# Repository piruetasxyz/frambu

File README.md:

# frambu

placa de desarrollo abierta basada en el microcontrolador **RP2040** de Raspberry Pi,
diseñada en [KiCad](https://www.kicad.org/) para fabricarse y ensamblarse en
[JLCPCB](https://jlcpcb.com/).

la documentación, con capturas del esquemático, de la placa y la lista de
materiales, está publicada en
[piruetasxyz.github.io/frambu](https://piruetasxyz.github.io/frambu/) y en
[`docs/frambu.md`](docs/frambu.md).

este repositorio se usa para trabajo colaborativo y también como material de
enseñanza: la idea es que cualquier persona pueda clonarlo, abrirlo, entender cómo
está hecho y modificarlo.

## contenidos

- [estado del proyecto](#estado-del-proyecto)
- [características de la placa](#características-de-la-placa)
- [estructura del repositorio](#estructura-del-repositorio)
- [automatizaciones (GitHub Actions)](#automatizaciones-github-actions)
- [requisitos](#requisitos)
- [cómo abrir el proyecto](#cómo-abrir-el-proyecto)
- [biblioteca local de KiCad](#biblioteca-local-de-kicad)
- [cómo trabajar en conjunto](#cómo-trabajar-en-conjunto)
- [pendientes conocidos](#pendientes-conocidos)
- [comentarios de revisión (2026-11-10)](#comentarios-de-revisión-2026-11-10)
- [glosario](#glosario)
- [recursos para aprender](#recursos-para-aprender)
- [licencia](#licencia)

## estado del proyecto

**revisión A, en diseño.** el esquemático está avanzado y la placa se está
rehaciendo desde cero: por ahora no tiene contorno, componentes ni pistas. no
está lista para fabricar.

| revisión | carpeta | estado |
| --- | --- | --- |
| A | [`frambu-v-0-rev-a/`](frambu-v-0-rev-a/) | en diseño |

## características de la placa

| bloque | componente | notas |
| --- | --- | --- |
| microcontrolador | RP2040 (U2), LQFN-56 7×7 mm | doble núcleo ARM Cortex-M0+, hasta 133 MHz |
| memoria flash | W25Q128JVS (U1), SOIC-8 | 128 Mbit (16 MB), conectada por QSPI |
| reloj | cristal Y1 de 12 MHz (ABM8-272-T3) + condensadores de 15 pF (C1, C2) | señales `XIN` / `XOUT` |
| USB | conector USB-C 16 pines (J1) | USB 2.0; resistencias de 5,1 kΩ en CC1/CC2 (R3, R4) para que el cable entregue 5 V; resistencias en serie de 27 Ω en `USB_D+`/`USB_D-` (R6, R7) |
| alimentación | regulador lineal AMS1117 (U3) | de `VBUS` (5 V del USB) a `+3V3`; el RP2040 genera internamente `+1V1` para su núcleo |
| botón | SW1 (PTS636) | botón de arranque (BOOTSEL), en la línea `QSPI_SS` |
| pines | J2 y J5, conectores hembra 1×20 de 2,54 mm | mismo pinout que la Raspberry Pi Pico: J2 son los pines 1–20 y J5 los pines 40–21 (el pin 1 de J5 es `VBUS`, así ambos conectores tienen el pin 1 en el mismo extremo). `VSYS` y `3V3_EN` quedan sin conexión |
| depuración | J3, conector macho 1×3 de 2,54 mm | `SWCLK`, `GND`, `SWD`, en el mismo orden que la Pico |
| GPIO extra | J4, conector hembra 1×4 de 2,54 mm | `GPIO23`, `GPIO24`, `GPIO25` y `GPIO29_ADC3`, que la Pico no expone |
| fijación | H1, H2 | agujeros para tornillos M3 |
| placa | 2 capas de cobre (`F.Cu`, `B.Cu`) | tamaño por definir: se está rehaciendo desde cero |

el diseño sigue de cerca la guía oficial
[Hardware design with RP2040](https://datasheets.raspberrypi.com/rp2040/hardware-design-with-rp2040.pdf),
que es la mejor referencia para entender por qué cada componente está ahí.

## estructura del repositorio

```text
frambu/
├── README.md                     este archivo
├── LICENSE                       licencia MIT
├── .gitignore                    ignora archivos temporales y de respaldo de KiCad
├── .github/workflows/            automatizaciones de GitHub Actions
├── docs/
│   ├── frambu.md              capturas y lista de materiales (BOM) de la placa
│   ├── generar_bom.py            regenera la tabla de BOM en frambu.md
│   └── images/                   capturas SVG generadas automáticamente
└── frambu-v-0-rev-a/              una carpeta por revisión de la placa
    ├── frambu-v-0-rev-a.kicad_pro proyecto de KiCad (abrir este)
    ├── frambu-v-0-rev-a.kicad_sch esquemático
    ├── frambu-v-0-rev-a.kicad_pcb diseño de la placa (PCB)
    ├── bom.csv                   lista de partes de JLCPCB, escrita a mano
    ├── sym-lib-table             registra la biblioteca local de símbolos
    ├── fp-lib-table              registra la biblioteca local de huellas
    └── bibliotecas/              biblioteca local generada desde bom.csv
        ├── frambu-v-0-rev-a.kicad_sym   símbolos
        ├── frambu-v-0-rev-a.pretty/     huellas (footprints)
        └── frambu-v-0-rev-a.3dshapes/   modelos 3D (.step y .wrl)
```

cada revisión vive en su propia carpeta para poder comparar versiones y no perder
el diseño de una placa ya fabricada.

## automatizaciones (GitHub Actions)

hay dos workflows en [`.github/workflows/`](.github/workflows/):

- [`actualizar-capturas.yml`](.github/workflows/actualizar-capturas.yml): cada
  vez que se hace push a `main` con cambios en el esquemático o la placa de la
  revisión activa, usa `kicad-cli` (KiCad 10, en docker) para exportar
  `docs/images/frambu-v-0-rev-a-esquematico.svg` y
  `docs/images/frambu-v-0-rev-a-placa.svg`, regenera la tabla de BOM en
  `docs/frambu.md` con `docs/generar_bom.py`, y hace commit de los cambios.
- [`desplegar-paginas.yml`](.github/workflows/desplegar-paginas.yml): construye
  el sitio con Jekyll y lo publica en GitHub Pages, tanto en cada push a `main`
  como al terminar el workflow anterior.

como el primer workflow hace commits, **conviene hacer `git pull` después de
cada push** que toque el esquemático o la placa.

la tabla de BOM también se puede regenerar a mano, con KiCad 10 instalado:

```bash
python3 docs/generar_bom.py
```

si se agrega una revisión nueva (por ejemplo `frambu-v-0-rev-b/`), hay que
actualizar las rutas en `actualizar-capturas.yml` y `REVISION` en
`docs/generar_bom.py`.

## requisitos

- **KiCad 10** o superior. los archivos se guardaron con KiCad 10.0 y no se
  pueden abrir en versiones anteriores.
- **git**, para clonar y colaborar.
- opcional, solo para regenerar la biblioteca local: **Python 3** y el
  repositorio [partes-jlcpcb](https://github.com/piruetasxyz/partes-jlcpcb).

## cómo abrir el proyecto

```bash
git clone https://github.com/piruetasxyz/frambu.git
cd frambu
```

luego, en KiCad: **Archivo → Abrir proyecto** y elegir
`frambu-v-0-rev-a/frambu-v-0-rev-a.kicad_pro`. desde ahí se abren el esquemático y
la placa.

no hace falta configurar nada más: los archivos `sym-lib-table` y `fp-lib-table`
del proyecto ya apuntan a la biblioteca local usando `${KIPRJMOD}`, que KiCad
reemplaza por la carpeta del proyecto. por eso funciona en cualquier computador,
sin importar dónde se clone el repositorio.

## biblioteca local de KiCad

las partes que usamos de JLCPCB se listan en `bom.csv` dentro de cada revisión
(por ejemplo `frambu-v-0-rev-a/bom.csv`). tiene las mismas columnas que el
inventario de [partes-jlcpcb](https://github.com/piruetasxyz/partes-jlcpcb):

| columna | significado |
| --- | --- |
| `Category` | tipo de componente |
| `Value` | valor (ej. `10kΩ`, `100nF`) o número de parte |
| `Footprint` | encapsulado (ej. `0402`, `SOIC-8`) |
| `JLCPCB Part #` | código LCSC, empieza con `C` (ej. `C25744`) |
| `Description` | descripción de JLCPCB |
| `Qty (fecha)` | cantidad en nuestro inventario en esa fecha; vacía si no la tenemos |

a partir de ese archivo se genera la biblioteca local (símbolos, huellas y
modelos 3D):

```bash
cd frambu-v-0-rev-a
python3 /ruta/a/partes-jlcpcb/generar_biblioteca.py --bom bom.csv --output bibliotecas/frambu-v-0-rev-a
```

ajusta `/ruta/a/partes-jlcpcb` a donde tengas clonado ese repositorio. requiere
su entorno virtual activado (ver su README).

### agregar una parte nueva

1. buscar la parte en [jlcpcb.com/parts](https://jlcpcb.com/parts) y anotar su
   código LCSC (`C…`). preferir partes **básicas** (*basic*) antes que
   **extendidas** (*extended*): las extendidas cobran un recargo de montaje por
   cada tipo de parte.
2. agregar una fila a `bom.csv`.
3. regenerar la biblioteca con el comando de arriba.
4. en el esquemático, usar el símbolo de la biblioteca `frambu-v-0-rev-a` o
   asignar la huella nueva al símbolo existente, y llenar su campo `LCSC` con el
   código de la parte.
5. hacer commit de `bom.csv` **y** de los archivos nuevos en `bibliotecas/`
   juntos, para que la otra persona no abra el proyecto con huellas faltantes.

## cómo trabajar en conjunto

los archivos de KiCad son texto, así que git los guarda bien, pero **no se
pueden fusionar (merge) de forma confiable**: si dos personas editan el mismo
`.kicad_sch` o `.kicad_pcb` a la vez, el conflicto casi siempre hay que
resolverlo a mano rehaciendo uno de los cambios. para evitarlo:

1. **avisar antes de editar.** decir quién está trabajando en el esquemático o
   en la placa, y no editar el mismo archivo al mismo tiempo.
2. **traer cambios antes de abrir KiCad:** `git pull`.
3. **cerrar KiCad antes de hacer commit**, para que todo esté guardado.
4. **commits pequeños y con mensajes claros**, en español y en minúsculas,
   describiendo el cambio (ej. `agregar cristal, mounting holes`).
5. **subir los cambios pronto:** `git push`, para que la otra persona los tenga.
6. para cambios grandes o experimentales, usar una rama y un pull request.

el `.gitignore` ya ignora lo que KiCad genera localmente y no debe subirse:
respaldos (`*-backups`), archivos de bloqueo (`~*.lck`), cachés,
`*.kicad_prl` (preferencias de ventana de cada persona) y archivos exportados
(`*.csv`, `*.xml`, `*.net`). la excepción es `bom.csv`, que sí se sube porque
lo escribimos a mano.

si KiCad dice que un archivo está bloqueado por otro usuario, probablemente
quedó un `~*.lck` de una sesión que se cerró mal; se puede borrar con KiCad
cerrado.

### antes de dar por terminada una revisión

- [ ] el esquemático pasa el **ERC** (Inspeccionar → Verificador de reglas
      eléctricas) sin errores.
- [ ] la placa pasa el **DRC** (Inspeccionar → Verificador de reglas de diseño)
      sin errores, usando las reglas de fabricación de JLCPCB.
- [ ] todos los componentes a ensamblar tienen código LCSC y huella que
      coincide con esa parte.
- [ ] la placa coincide con el esquemático (Herramientas → Actualizar PCB desde
      el esquemático, sin cambios pendientes).
- [ ] revisado en el visor 3D.

## pendientes conocidos

revisión A, a la fecha de este documento:

- la placa está vacía: falta dibujar el contorno en `Edge.Cuts` (antes era de
  50 × 60 mm), traer las huellas desde el esquemático (`F8`), ubicarlas y rutear.
- varias partes del esquemático no están en el inventario de
  [`partes-jlcpcb`](https://github.com/piruetasxyz/partes-jlcpcb), solo en su
  lista de deseos: U3 (`C880752`), R2 (`C25744`), C3, C7, C18 (`C15525`),
  R6, R7 (`C25100`), C1, C2 (`C1548`), Y1 (`C20625731`) y los condensadores de
  100 nF C5, C8–C12, C15, C16, C19 (`C307331`).
- al ubicar J2 y J5, sus pines 1 van en el mismo extremo de la placa, separados
  por 17,78 mm (7 × 2,54 mm) como en la Pico, para que sea compatible con sus
  accesorios.
- `VSYS` (pin 39 de la Pico) queda sin conexión. para alimentar la placa por ahí,
  como en la Pico, falta un diodo Schottky de `VBUS` a `VSYS` y alimentar U3
  desde `VSYS`.

## comentarios de revisión (2026-11-10)

notas de la revisión de hoy, para que alguien más las revise antes de mandar a
fabricar.

### cambios hechos

- **anillos anulares:** tres vías de `GND` medían 0,45 mm con taladro de 0,3 mm
  (anillo de 0,075 mm, el mínimo es 0,1 mm). se agrandaron a 0,6 mm, como el
  resto de las vías. después se corrigieron a mano los problemas de margen que
  eso generó.
- **C16** (100 nF, desacople de `+3V3`) estaba en el esquemático pero no en la
  placa; ya está ubicado y ruteado.
- **GPIO23, GPIO24, GPIO25 y GPIO29_ADC3** del RP2040 ahora están marcados como
  sin conexión (`X`) en el esquemático, y sus pads en la placa coinciden. en la
  Pico esos pines se usan internamente y no salen a los conectores. se prefirió
  dejarlos sin conexión en vez de llevarlos a `GND`, porque si el firmware los
  configura como salida en alto quedarían en corto.
- **archivos de fabricación:** nuevo script
  [`docs/generar_fabricacion.py`](docs/generar_fabricacion.py), que genera con
  `kicad-cli` las mismas carpetas que se usaron en
  [tacto48](https://github.com/piruetasxyz/tacto48):
  - [`frambu-v-0-rev-a-fab/`](frambu-v-0-rev-a-fab/): gerbers, taladros (PTH y
    NPTH), `gbrjob` y `frambu-v-0-rev-a-gerb.zip`, que es lo que se sube a
    JLCPCB como "Gerber file".
  - [`frambu-v-0-rev-a-pcba/`](frambu-v-0-rev-a-pcba/): `bom.csv` y `cpl.csv`
    para "PCB Assembly". entran todas las partes con el campo `LCSC` lleno en el
    esquemático; J2, J3 y J5 (conectores de 2,54 mm) quedan fuera y se sueldan
    a mano.
  - se regeneran con `python3 docs/generar_fabricacion.py` (requiere KiCad 10).
  - el `.gitignore` ahora deja pasar `*-pcba/*.csv`.

estado al cerrar la revisión: el DRC no tiene errores ni conexiones pendientes,
la placa coincide con el esquemático, y el ERC no tiene errores ni avisos. solo
quedan 19 avisos de serigrafía recortada por la máscara (los círculos de pin 1
de los condensadores y resistencias 0402), que no afectan la fabricación.

### por revisar

- [ ] **J1 (USB-C) en la vista previa de JLCPCB:** el origen de la huella de
  KiCad está corrido 1,5 mm respecto al centro de sus pads, así que JLCPCB
  podría mostrarlo desplazado. corregir en el `cpl.csv` si hace falta.
- [ ] **rotación de U2 (RP2040) e Y1 (cristal):** usan huellas de la biblioteca
  estándar de KiCad, que a veces no coinciden en rotación con JLCPCB. revisar
  que el punto del pin 1 calce.
- [ ] el resto de las piezas usa huellas generadas desde EasyEDA, que en general
  ya calzan con JLCPCB, pero conviene mirarlas igual.
- [ ] **este README está desactualizado** en varias partes: dice que la placa
  está vacía y que "no está lista para fabricar", menciona un conector J4 con
  GPIO23–25 y GPIO29 (no existe, y esos pines ahora están sin conexión) y
  agujeros M3 H1 y H2 (no están en la placa).

## glosario

| término | significado |
| --- | --- |
| **esquemático** | el dibujo de qué está conectado con qué, sin importar la posición física |
| **PCB** | *printed circuit board*, placa de circuito impreso; también el archivo con el diseño físico |
| **huella** (*footprint*) | la forma de cobre en la placa donde se suelda un componente |
| **símbolo** | cómo se dibuja un componente en el esquemático |
| **net** | una conexión eléctrica: todos los pines unidos por un mismo cable lógico |
| **pista** (*track*) | línea de cobre que conecta pines en la placa |
| **ERC / DRC** | verificaciones automáticas de reglas eléctricas / de diseño |
| **BOM** | *bill of materials*, lista de materiales |
| **LCSC** | distribuidor asociado a JLCPCB; sus códigos `C…` identifican cada parte |
| **SMD** | componente de montaje superficial (sin patitas que atraviesan la placa) |
| **0402, 0805, 1206** | tamaños estándar de componentes SMD en pulgadas (0805 = 0,08 × 0,05 in) |
| **QSPI** | bus de 4 líneas de datos con el que el RP2040 lee su memoria flash |
| **SWD** | *serial wire debug*, interfaz para programar y depurar el microcontrolador |
| **BOOTSEL** | modo en que el RP2040 aparece como unidad USB para cargarle programas |
| **LDO** | regulador lineal de baja caída; aquí baja 5 V a 3,3 V |

## recursos para aprender

- [documentación de KiCad](https://docs.kicad.org/) (disponible en español).
- [Hardware design with RP2040](https://datasheets.raspberrypi.com/rp2040/hardware-design-with-rp2040.pdf):
  guía oficial con un diseño mínimo de referencia, muy parecido a esta placa.
- [hoja de datos del RP2040](https://datasheets.raspberrypi.com/rp2040/rp2040-datasheet.pdf).
- [capacidades de fabricación de JLCPCB](https://jlcpcb.com/capabilities/pcb-capabilities):
  tamaños mínimos de pista, separación y perforaciones para configurar el DRC.

## licencia

[MIT](LICENSE), © 2026 piruetas.

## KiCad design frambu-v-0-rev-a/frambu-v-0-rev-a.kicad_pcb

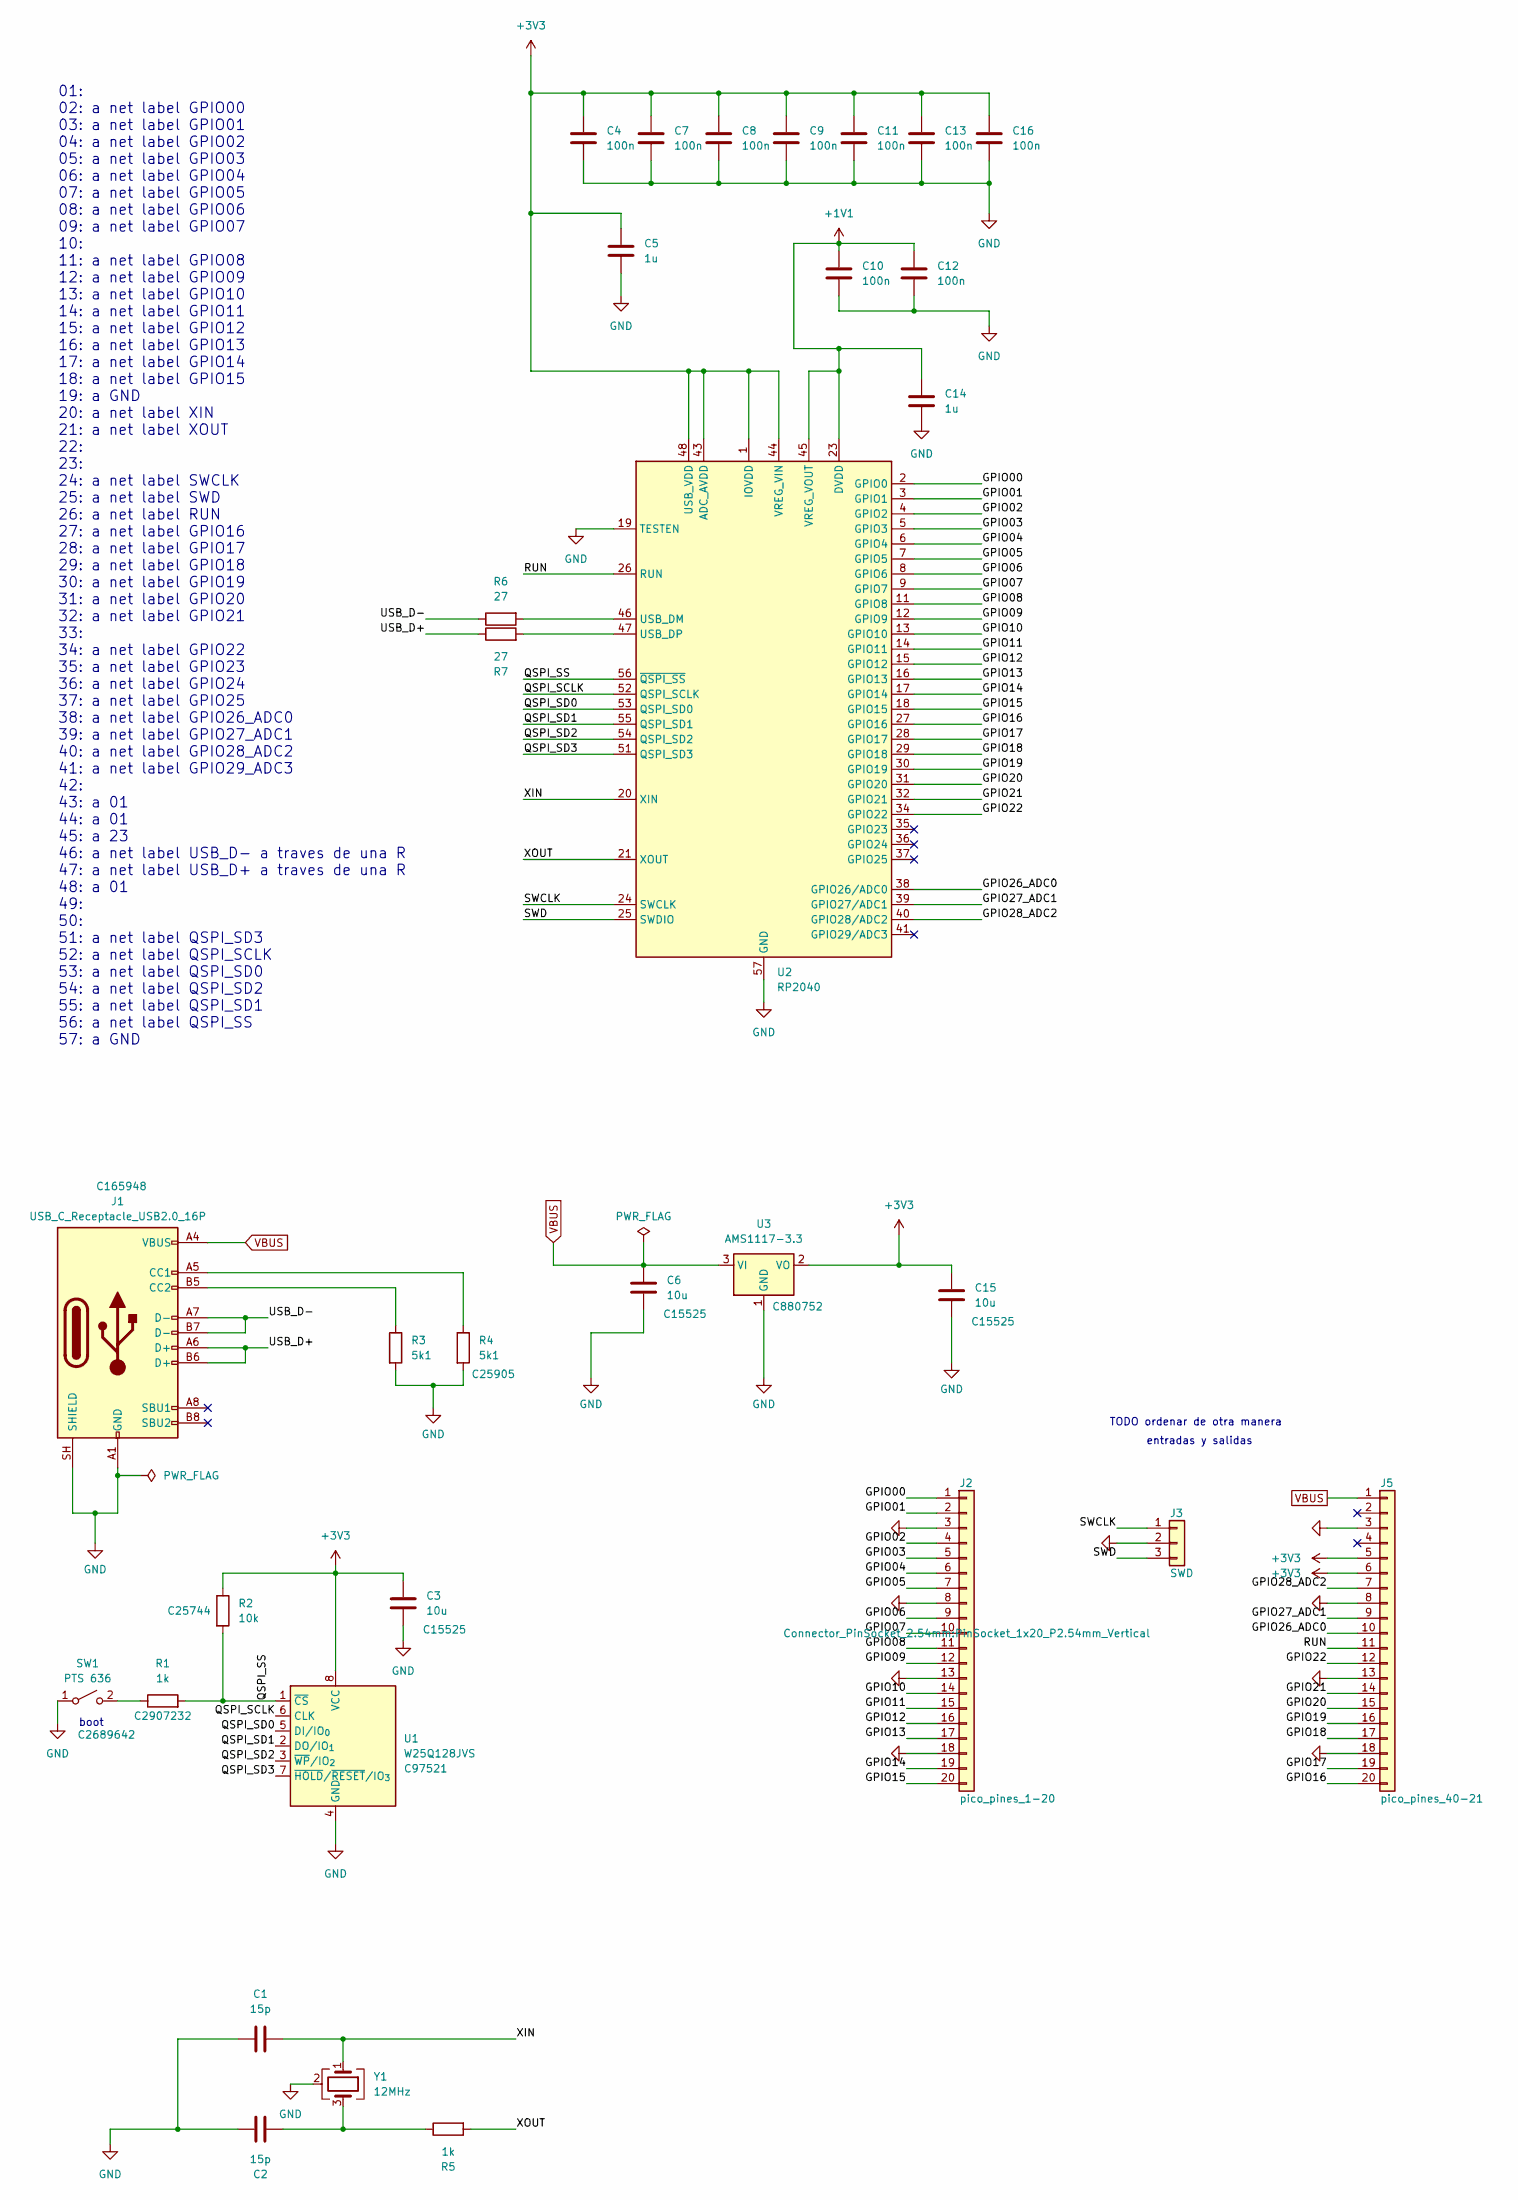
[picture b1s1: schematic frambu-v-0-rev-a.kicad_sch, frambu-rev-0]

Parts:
C1, C2: 15p; C0402; LCSC C1548
C3, C6, C15: 10u; C0402; LCSC C15525
C4, C7, C8, C9, C10, C11, C12, C13, C16: 100n; C0402; LCSC C307331
C5, C14: 1u; C_0805_2012Metric; LCSC C77083
J1: USB_C_Receptacle_USB2.0_16P; USB_C_Receptacle_HRO_TYPE-C-31-M-12; LCSC C165948
J2: pico_pines_1-20; PinSocket_1x20_P2.54mm_Vertical
J3: SWD; PinHeader_1x03_P2.54mm_Vertical
J5: pico_pines_40-21; PinSocket_1x20_P2.54mm_Vertical
R1, R5: 1k; R_0805_2012Metric; LCSC C2907232
R2: 10k; R0402; LCSC C25744
R3, R4: 5k1; R0402; LCSC C25905
R6, R7: 27; R0402; LCSC C25100
SW1: PTS 636; KEY-SMD_L6.0-W3.5-LS8.7; LCSC C2689642
U1: W25Q128JVS; SOIC-8_L5.3-W5.3-P1.27-LS8.0-BL; LCSC C97521
U2: RP2040; QFN-56-1EP_7x7mm_P0.4mm_EP3.2x3.2mm; LCSC C2040
U3: AMS1117-3.3; SOT-89-3_L4.5-W2.5-P1.50-LS4.2-BR; LCSC C880752
Y1: 12MHz; Crystal_SMD_3225-4Pin_3.2x2.5mm; LCSC C20625731

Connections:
+1V1: C10.1, C12.1, C14.1, U2.23 (DVDD), U2.45 (VREG_VOUT), U2.50 (DVDD)
+3V3: C3.1, C4.1, C5.1, C7.1, C8.1, C9.1, C11.1, C13.1, C15.1, C16.1, J5.5, J5.6, R2.1, U1.8 (VCC), U2.1 (IOVDD), U2.10 (IOVDD), U2.22 (IOVDD), U2.33 (IOVDD), U2.42 (IOVDD), U2.43 (ADC_AVDD), U2.44 (VREG_VIN), U2.48 (USB_VDD), U2.49 (IOVDD), U3.2 (VO)
/GPIO00: J2.1, U2.2 (GPIO0)
/GPIO01: J2.2, U2.3 (GPIO1)
/GPIO02: J2.4, U2.4 (GPIO2)
/GPIO03: J2.5, U2.5 (GPIO3)
/GPIO04: J2.6, U2.6 (GPIO4)
/GPIO05: J2.7, U2.7 (GPIO5)
/GPIO06: J2.9, U2.8 (GPIO6)
/GPIO07: J2.10, U2.9 (GPIO7)
/GPIO08: J2.11, U2.11 (GPIO8)
/GPIO09: J2.12, U2.12 (GPIO9)
/GPIO10: J2.14, U2.13 (GPIO10)
/GPIO11: J2.15, U2.14 (GPIO11)
/GPIO12: J2.16, U2.15 (GPIO12)
/GPIO13: J2.17, U2.16 (GPIO13)
/GPIO14: J2.19, U2.17 (GPIO14)
/GPIO15: J2.20, U2.18 (GPIO15)
/GPIO16: J5.20, U2.27 (GPIO16)
/GPIO17: J5.19, U2.28 (GPIO17)
/GPIO18: J5.17, U2.29 (GPIO18)
/GPIO19: J5.16, U2.30 (GPIO19)
/GPIO20: J5.15, U2.31 (GPIO20)
/GPIO21: J5.14, U2.32 (GPIO21)
/GPIO22: J5.12, U2.34 (GPIO22)
/GPIO26_ADC0: J5.10, U2.38 (GPIO26/ADC0)
/GPIO27_ADC1: J5.9, U2.39 (GPIO27/ADC1)
/GPIO28_ADC2: J5.7, U2.40 (GPIO28/ADC2)
/QSPI_SCLK: U1.6 (CLK), U2.52 (QSPI_SCLK)
/QSPI_SD0: U1.5 (DI/IO_{0}), U2.53 (QSPI_SD0)
/QSPI_SD1: U1.2 (DO/IO_{1}), U2.55 (QSPI_SD1)
/QSPI_SD2: U1.3 (~WP/IO_{2}), U2.54 (QSPI_SD2)
/QSPI_SD3: U1.7 (~HOLD/~RESET/IO_{3}), U2.51 (QSPI_SD3)
/QSPI_SS: R1.2, R2.2, U1.1 (~CS), U2.56 (~QSPI_SS)
/RUN: J5.11, U2.26 (RUN)
/SWCLK: J3.1, U2.24 (SWCLK)
/SWD: J3.3, U2.25 (SWDIO)
/USB_D+: J1.A6 (D+), J1.B6 (D+), R7.1
/USB_D-: J1.A7 (D-), J1.B7 (D-), R6.1
/XIN: C1.2, U2.20 (XIN), Y1.1
/XOUT: R5.2, U2.21 (XOUT)
GND: C1.1, C2.1, C3.2, C4.2, C5.2, C6.2, C7.2, C8.2, C9.2, C10.2, C11.2, C12.2, C13.2, C14.2, C15.2, C16.2, J1.A1 (GND), J1.A12 (GND), J1.B1 (GND), J1.B12 (GND), J1.SH (SHIELD), J2.3, J2.8, J2.13, J2.18, J3.2, J5.3, J5.8, J5.13, J5.18, R3.2, R4.2, SW1.1 (A), U1.4 (GND), U2.19 (TESTEN), U2.57 (GND), U3.1 (GND), Y1.2 (G), Y1.4 (G)
unnamed: C2.2, R5.1, Y1.3
unnamed: J1.A5 (CC1), R4.1
unnamed: J1.B5 (CC2), R3.1
unnamed: R1.1, SW1.2 (B)
unnamed: R6.2, U2.46 (USB_DM)
unnamed: R7.2, U2.47 (USB_DP)
VBUS: C6.1, J1.A4 (VBUS), J1.A9 (VBUS), J1.B4 (VBUS), J1.B9 (VBUS), J5.1, U3.3 (VI)

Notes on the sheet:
entradas y salidas
boot
01: 02: a net label GPIO00 03: a net label GPIO01 04: a net label GPIO02 05: a net label GPIO03 06: a net label GPIO04 07: a net label GPIO05 08: a net label GPIO06 09: a net label GPIO07 10: 11: a net label GPIO08 12: a net label GPIO09 13: a net label GPIO10 14: a net label GPIO11 15: a net label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
TODO ordenar de otra manera

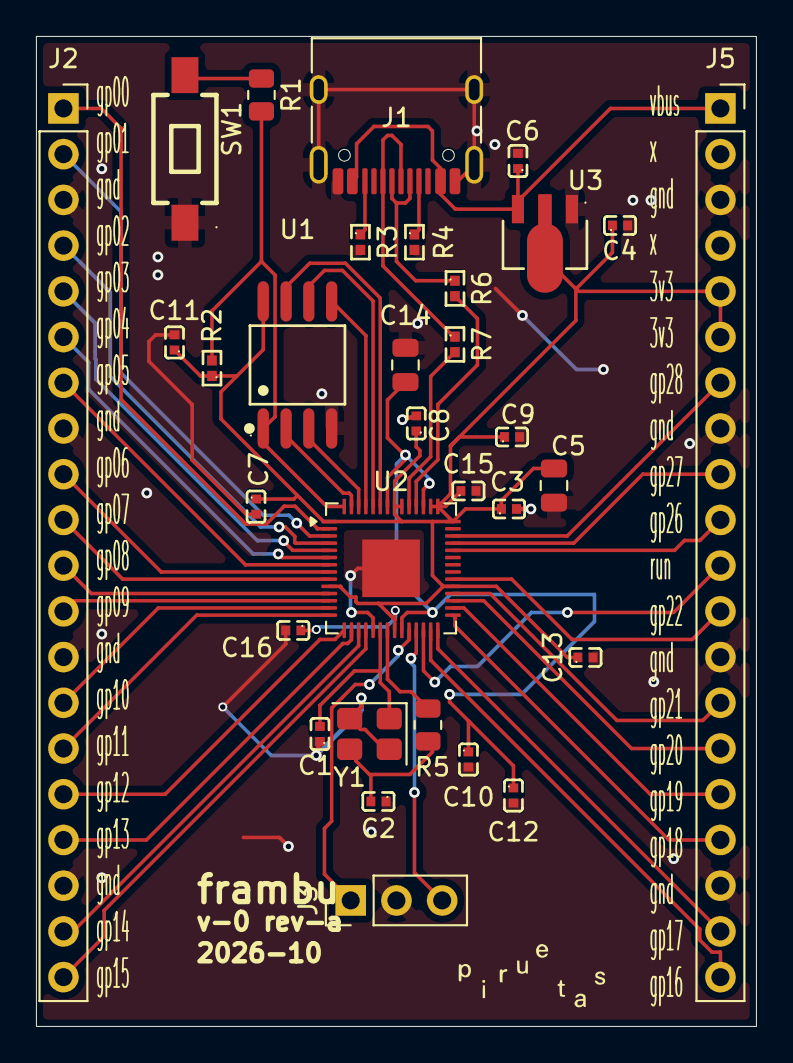
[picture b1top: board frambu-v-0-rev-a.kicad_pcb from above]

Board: 2 copper layers, 40.0 x 55.0 mm, 32 parts (0 on the bottom side), 49 nets.

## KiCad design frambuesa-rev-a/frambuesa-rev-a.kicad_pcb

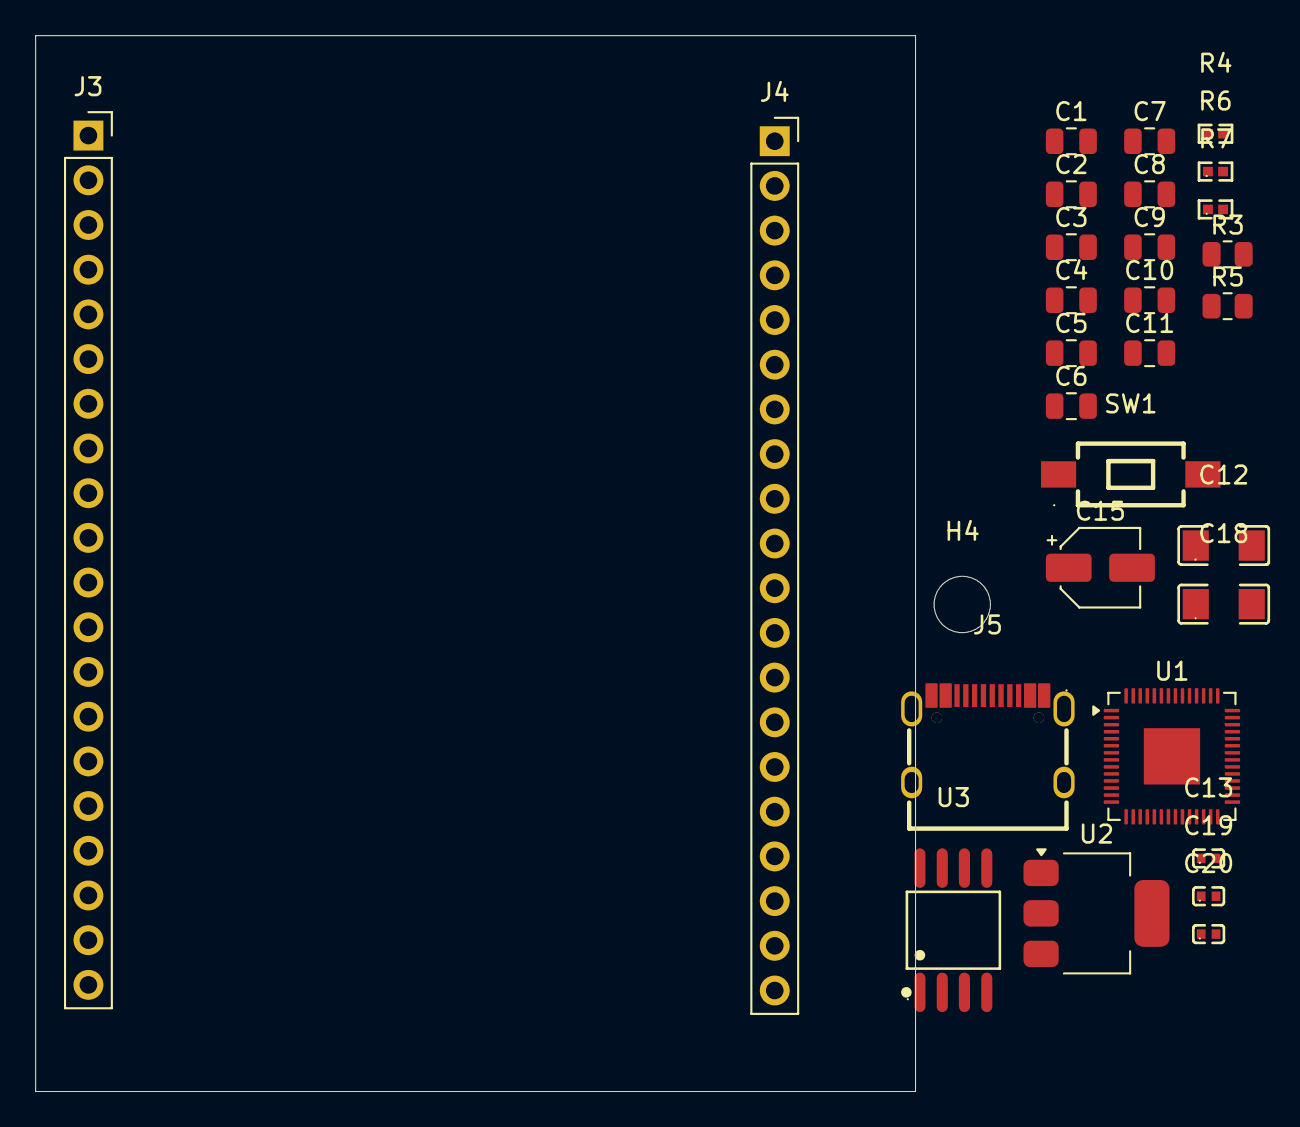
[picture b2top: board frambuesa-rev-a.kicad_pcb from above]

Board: 2 copper layers, 50.0 x 60.0 mm, 30 parts (0 on the bottom side), 36 nets, no tracks yet.

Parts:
C1, C9: 1u; C_0805_2012Metric
C2, C3, C4, C5, C6, C7, C8, C10, C11: 100n; C_0805_2012Metric
C12, C18: 100u; C1206
C13, C19, C20: 10u; C0402
C15: 10u; CP_Elec_4x5.4
H4: MountingHole; MountingHole_3.2mm_M3
J3, J4: Conn_02x18_Odd_Even; PinSocket_1x20_P2.54mm_Vertical
J5: USB_C_Receptacle_USB2.0_16P; USB-C_SMD-TYPE-C-31-M-12_1
R3: 1k; R_0805_2012Metric
R4: 10k; R0402
R5: 1K; R_0805_2012Metric
R6, R7: 5k1; R0402
SW1: PTS 636; KEY-SMD_L6.0-W3.5-LS8.7
U1: RP2040; QFN-56-1EP_7x7mm_P0.4mm_EP3.2x3.2mm
U2: AMS1117-5.0; SOT-223-3_TabPin2
U3: W25Q128JVS; SOIC-8_L5.3-W5.3-P1.27-LS8.0-BL

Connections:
+1V1: C9.1, C10.1, C11.1, U1.23 (DVDD), U1.45 (VREG_VOUT), U1.50 (DVDD)
+3.3V: C18.1, C19.1, U2.2 (VO)
+3V3: C1.1, C2.1, C3.1, C4.1, C5.1, C6.1, C7.1, C8.1, C15.1, C20.1, J3.2, R4.1, U1.1 (IOVDD), U1.10 (IOVDD), U1.22 (IOVDD), U1.33 (IOVDD), U1.42 (IOVDD), U1.43 (ADC_AVDD), U1.44 (VREG_VIN), U1.48 (USB_VDD), U1.49 (IOVDD), U3.8 (VCC)
/GPIO00: J3.4, U1.2 (GPIO0)
/GPIO01: J3.6, U1.3 (GPIO1)
/GPIO02: J3.8, U1.4 (GPIO2)
/GPIO03: J3.10, U1.5 (GPIO3)
/GPIO04: J3.12, U1.6 (GPIO4)
/GPIO05: J3.14, U1.7 (GPIO5)
/GPIO06: J3.16, U1.8 (GPIO6)
/GPIO07: J3.18, U1.9 (GPIO7)
/GPIO08: J3.20, U1.11 (GPIO8)
/GPIO20: J4.19, U1.31 (GPIO20)
/GPIO21: J4.17, U1.32 (GPIO21)
/GPIO22: J4.15, U1.34 (GPIO22)
/GPIO23: J4.13, U1.35 (GPIO23)
/GPIO24: J4.11, U1.36 (GPIO24)
/GPIO25: J4.9, U1.37 (GPIO25)
/GPIO26_ADC0: J4.7, U1.38 (GPIO26/ADC0)
/GPIO27_ADC1: J4.5, U1.39 (GPIO27/ADC1)
/GPIO28_ADC2: J4.3, U1.40 (GPIO28/ADC2)
/GPIO29_ADC3: J4.1, U1.41 (GPIO29/ADC3)
/QSPI_SCLK: U1.52 (QSPI_SCLK), U3.6 (CLK)
/QSPI_SD0: U1.53 (QSPI_SD0), U3.5 (DI/IO_{0})
/QSPI_SD1: U1.55 (QSPI_SD1), U3.2 (DO/IO_{1})
/QSPI_SD2: U1.54 (QSPI_SD2), U3.3 (~WP/IO_{2})
/QSPI_SD3: U1.51 (QSPI_SD3), U3.7 (~HOLD/~RESET/IO_{3})
/QSPI_SS: R3.2, R4.2, U3.1 (~CS)
/USB_D+: J5.A6 (D+), J5.B6 (D+)
/USB_D-: J5.A7 (D-), J5.B7 (D-)
/XOUT: R5.2, U1.21 (XOUT)
GND: C1.2, C2.2, C3.2, C4.2, C5.2, C6.2, C7.2, C8.2, C9.2, C10.2, C11.2, C12.2, C13.2, C15.2, C18.2, C19.2, C20.2, J3.1, J3.3, J3.5, J3.7, J3.9, J3.11, J3.13, J3.15, J3.17, J3.19, J4.2, J4.4, J4.6, J4.8, J4.10, J4.12, J4.14, J4.16, J4.18, J4.20, R6.2, R7.2, SW1.1 (A), U1.19 (TESTEN), U1.57 (GND), U2.1 (GND), U3.4 (GND)
unnamed: J5.A5 (CC1), R6.1
unnamed: J5.B5 (CC2), R7.1
unnamed: R3.1, SW1.2 (B)
VHI: C12.1, C13.1, U2.3 (VI)
